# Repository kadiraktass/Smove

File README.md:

# Solutions for Smove challenges 

In this repo, you can find my solutions for firmware and hardware challenges of [Smove challenges](https://github.com/itatsmove/smovechallenge).

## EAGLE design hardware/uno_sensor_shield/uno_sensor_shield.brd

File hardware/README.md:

# Hardware challenge solution  

[Desired hardware](https://github.com/itatsmove/smovechallenge/blob/master/challenges/hardware.md) is designed using [Eagle 9.1.0](https://www.autodesk.com/products/eagle/overview). Design files, BOM and Gerber files are included in [uno_sensor_shield](https://github.com/kadiraktass/Smove/tree/master/hardware/uno_sensor_shield) folder. 

Arduino Uno shield package is used for board outline and arduino pins. Board is built on this object.  

I2C signals are pulled up and passed through a bidirectional 5v-3v3 voltage level shifter before connecting to ICs.  

All the parts used in the design and battery cell holder and headers for Arduino are included in BOM. 

PCB has two layers, top and bottom. Both layers are filled with Ground. 

Power lines are drawn thicker compared to signal lines. 

Design can be changed to provide certain requirements such as dimensions.  

## Libraries 

The following libraries are used for missing footprints:  
[MPU9250](https://componentsearchengine.com/MPU-9250/InvenSense+Inc.)  
[OPT3001](https://componentsearchengine.com/part.php?partID=300356)  
[PCF8523T](https://componentsearchengine.com/part.php?partID=274221)  
[BMP280](https://componentsearchengine.com/part.php?partID=237787)  
[CR1220 and Uno Shield Package](https://github.com/adafruit/Adafruit-Eagle-Library)  
[BSS138](https://componentsearchengine.com/part.php?partID=232961)  
[JTX210](https://componentsearchengine.com/part.php?partID=1253227)

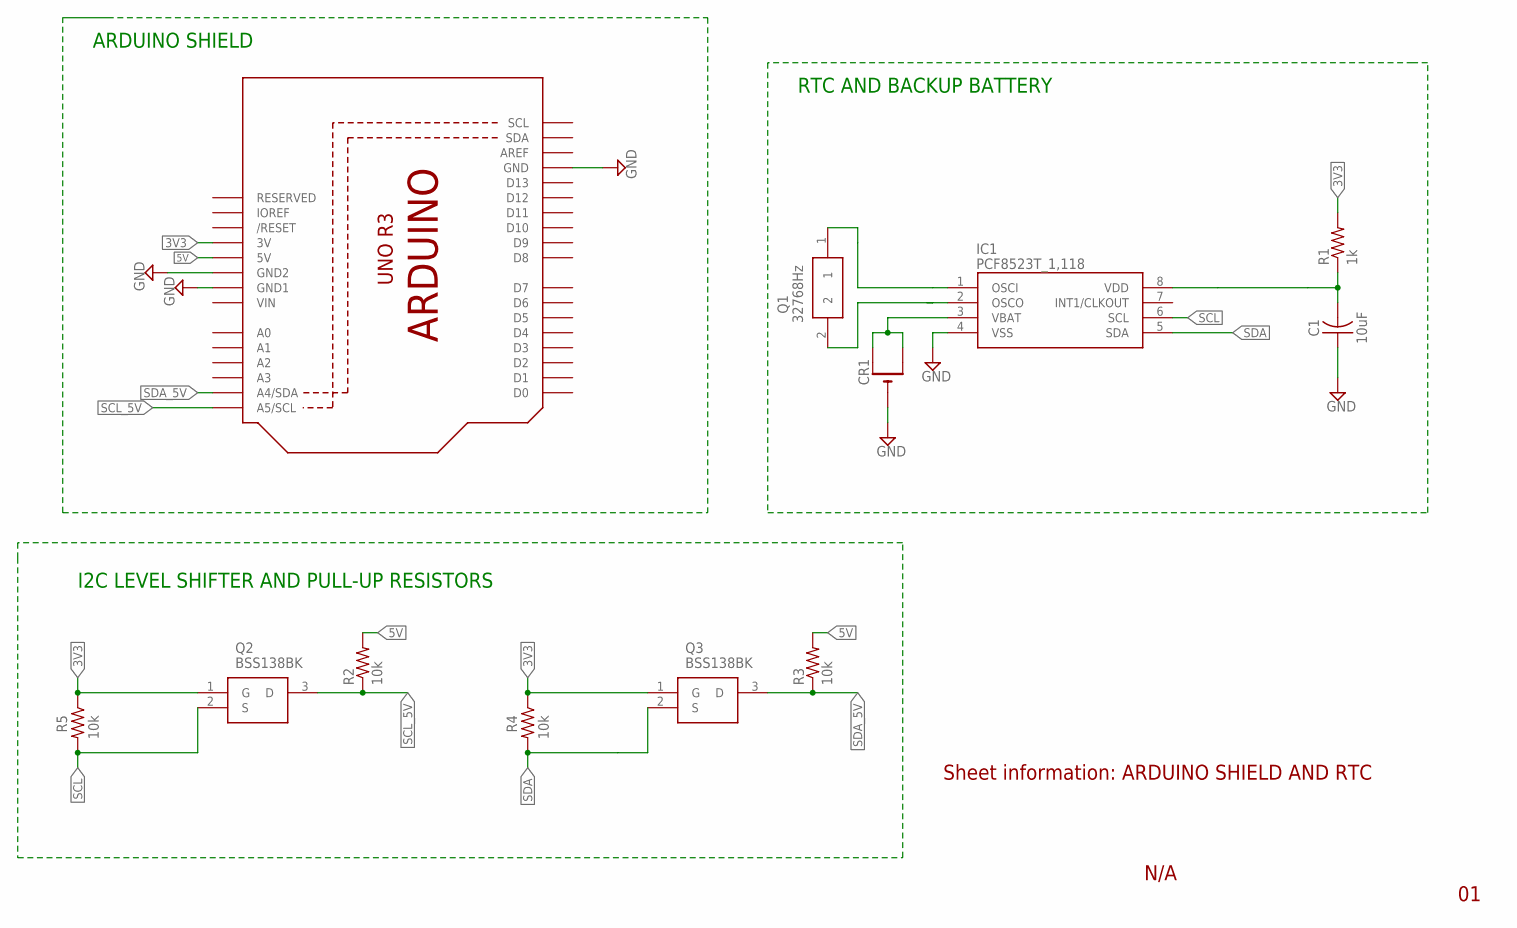
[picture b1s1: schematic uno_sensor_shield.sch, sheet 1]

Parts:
C1: 10uF; C0805
CR1: CR1220SMT; CR1220-SMD
IC1: PCF8523T_1,118; SOIC127P600X175-8N
Q1: 32768Hz; Q0032768JTX21012520T1LF
Q2, Q3: BSS138BK; SOT95P230X110-3N
R1: 1k; R0805
R2, R3, R4, R5: 10k; R0805
U1: ARDUINOR3-DIMENSION; ARDUINOR3

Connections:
3V3: Q2.1 (G), Q3.1 (G), R1.2, R4.1, R5.1, U1.3V; also elsewhere on the board
5V: R2.2, R3.2, U1.5V
GND: C1.1, CR1.-, IC1.4 (VSS), U1.GND, U1.GND1, U1.GND2; also elsewhere on the board
unnamed: IC1.2 (OSCO), Q1.2
unnamed: C1.2, IC1.8 (VDD), R1.1
unnamed: IC1.1 (OSCI), Q1.1
SCL: IC1.6 (SCL), Q2.2 (S), R5.2; also elsewhere on the board
SCL_5V: Q2.3 (D), R2.1, U1.A5 (A5/SCL)
SDA: IC1.5 (SDA), Q3.2 (S), R4.2; also elsewhere on the board
SDA_5V: Q3.3 (D), R3.1, U1.A4 (A4/SDA)
VBAT: CR1.+$1 (+), CR1.+$2 (+1), IC1.3 (VBAT)
VIN: U1.VIN

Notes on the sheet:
I2C LEVEL SHIFTER AND PULL-UP RESISTORS
N/A
Sheet information: ARDUINO SHIELD AND RTC
ARDUINO SHIELD
RTC AND BACKUP BATTERY

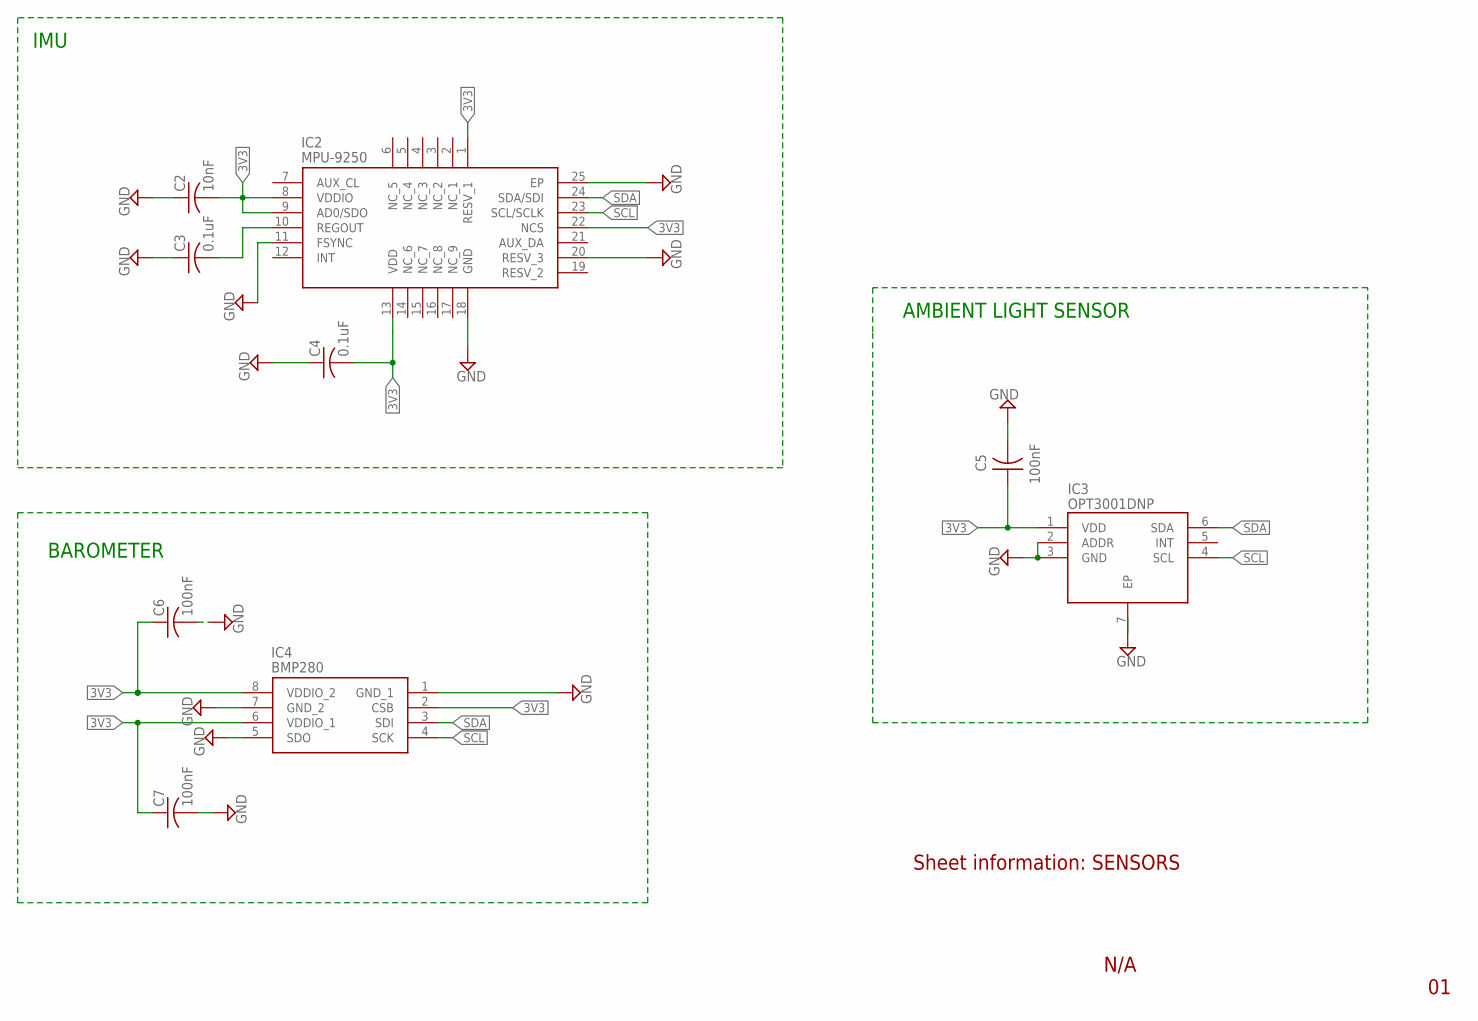
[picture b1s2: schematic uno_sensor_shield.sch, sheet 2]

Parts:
C2: 10nF; C0805
C3, C4: 0.1uF; C0805
C5, C6, C7: 100nF; C0805
IC2: MPU-9250; QFN40P300X300X105-25N
IC3: OPT3001DNP; SON65P200X200X65-7N
IC4: BMP280; 8-PIN-METAL-LID-LGA

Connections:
3V3: C2.2, C4.2, C5.1, C6.1, C7.1, IC2.1 (RESV_1), IC2.8 (VDDIO), IC2.9 (AD0/SDO), IC2.13 (VDD), IC2.22 (NCS), IC3.1 (VDD), IC4.2 (CSB), IC4.6 (VDDIO_1), IC4.8 (VDDIO_2); also elsewhere on the board
GND: C2.1, C3.1, C4.1, C5.2, C6.2, C7.2, IC2.11 (FSYNC), IC2.18 (GND), IC2.20 (RESV_3), IC2.25 (EP), IC3.2 (ADDR), IC3.3 (GND), IC3.7 (EP), IC4.1 (GND_1), IC4.5 (SDO), IC4.7 (GND_2); also elsewhere on the board
unnamed: C3.2, IC2.10 (REGOUT)
SCL: IC2.23 (SCL/SCLK), IC3.4 (SCL), IC4.4 (SCK); also elsewhere on the board
SDA: IC2.24 (SDA/SDI), IC3.6 (SDA), IC4.3 (SDI); also elsewhere on the board

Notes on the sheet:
Sheet information: SENSORS
N/A
IMU
BAROMETER
AMBIENT LIGHT SENSOR

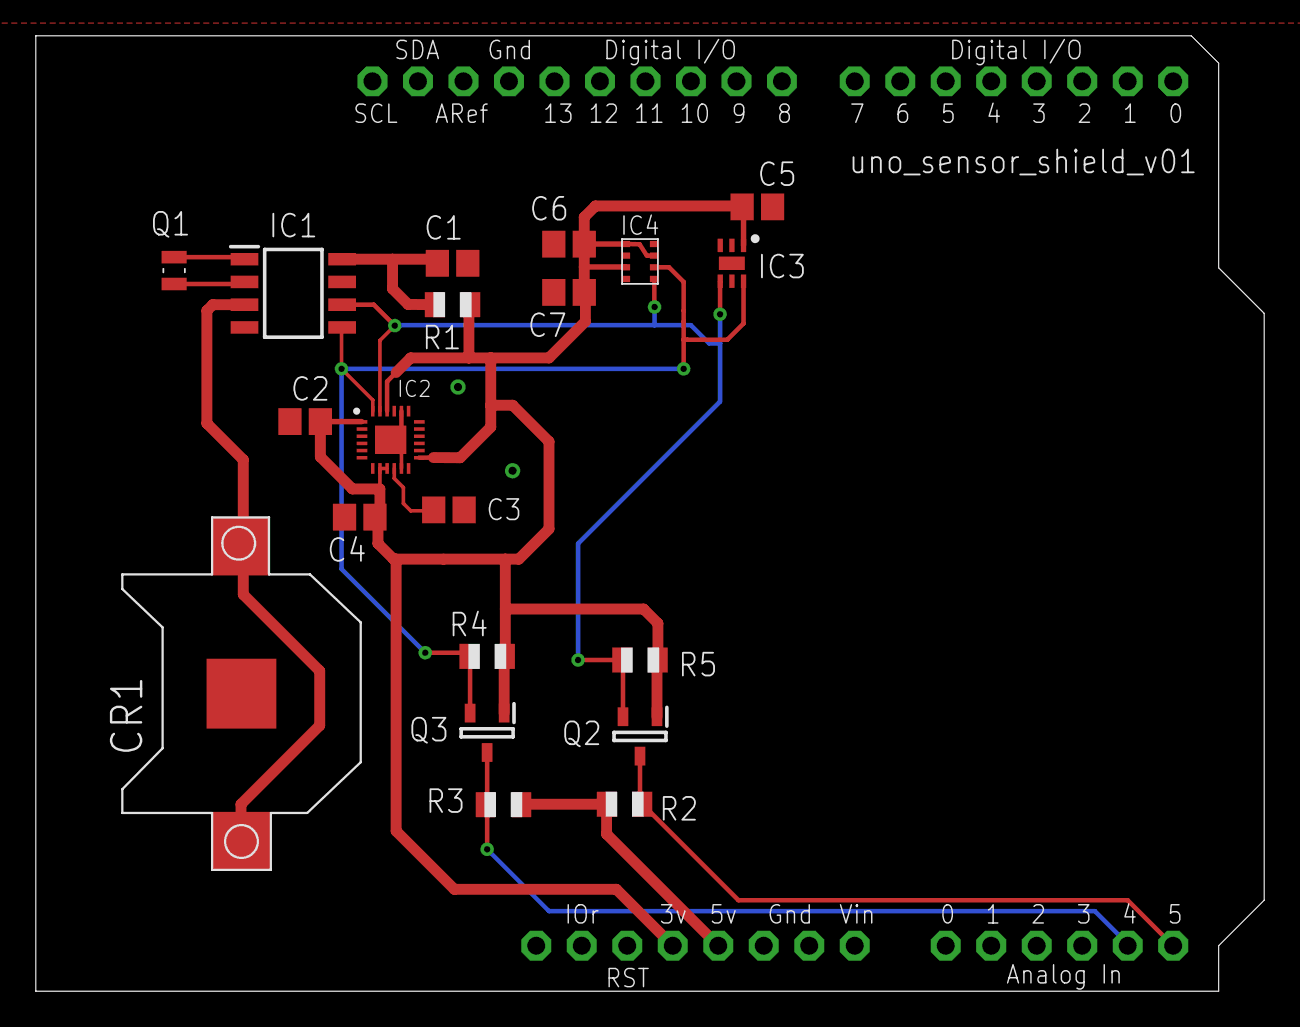
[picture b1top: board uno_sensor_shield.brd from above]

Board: 2 copper layers, 68.6 x 53.3 mm, 21 parts (0 on the bottom side), 12 nets.

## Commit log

2018-07-25 solutions are updated
2018-07-25 solutions are added
2018-07-25 readme update
2018-07-26 Remove typo
